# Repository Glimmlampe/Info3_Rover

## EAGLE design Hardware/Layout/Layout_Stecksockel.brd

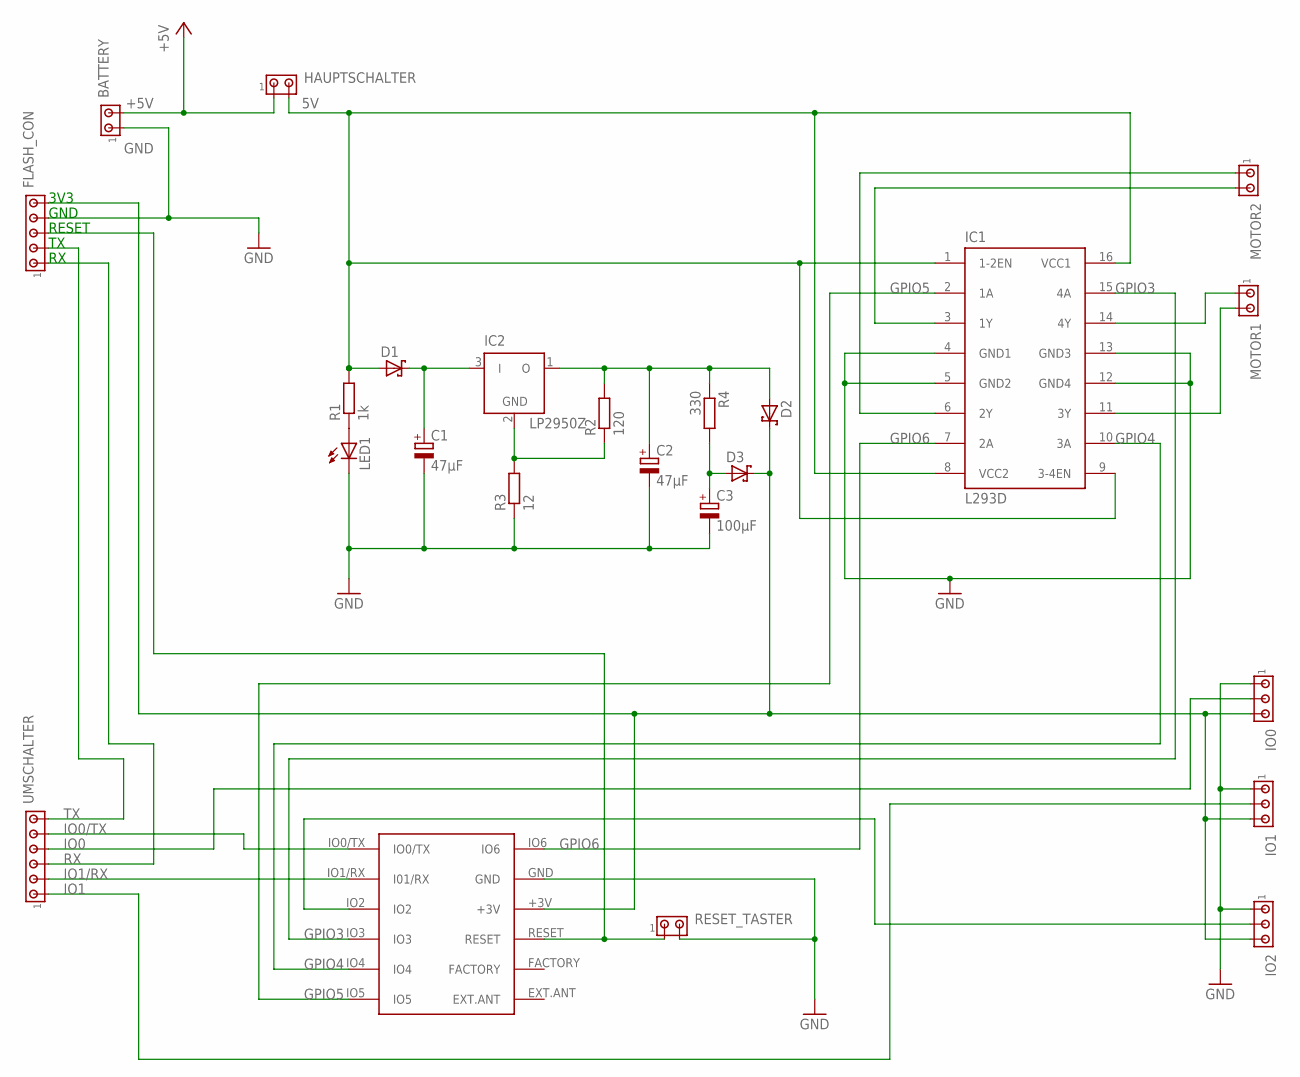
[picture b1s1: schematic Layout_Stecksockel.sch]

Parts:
BATTERY: MTA02-100; 10X02MTA
C1, C2: 47µF; E2,5-6E
C3: 100µF; E2,5-6E
D1, D2, D3: SCHOTTKY-DIODEDO35-7; DO35-7
FLASH_CON: MTA05-100; 10X05MTA
HAUPTSCHALTER: MTA02-100; 10X02MTA
IC1: L293D; DIL16
IC2: LP2950Z; TO92
IO0, IO1, IO2: MTA03-100; 10X03MTA
LED1: LED_ELD260; LED_LD260
MOTOR1, MOTOR2: MTA02-100; 10X02MTA
R1: 1k; 0207/10
R2: 120; 0207/10
R3: 12; 0207/10
R4: 330; 0207/10
RESET_TASTER: MTA02-100; 10X02MTA
U$1: RFDUINO
UMSCHALTER: MTA06-100; 10X06MTA

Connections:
5V: D1.A, HAUPTSCHALTER.2, IC1.1 (1-2EN), IC1.8 (VCC2), IC1.9 (3-4EN), IC1.16 (VCC1), R1.2
+3V: D2.C, D3.C, FLASH_CON.5, IO0.3, IO1.3, IO2.3, U$1.+3V
+5V: BATTERY.2, HAUPTSCHALTER.1
GND: BATTERY.1, C1.-, C2.-, C3.-, FLASH_CON.4, IC1.4 (GND1), IC1.5 (GND2), IC1.12 (GND4), IC1.13 (GND3), IO0.1, IO1.1, IO2.1, LED1.K (C), R3.1, RESET_TASTER.2, U$1.GND
GPIO3: IC1.15 (4A), U$1.IO3
GPIO4: IC1.10 (3A), U$1.IO4
GPIO5: IC1.2 (1A), U$1.IO5
GPIO6: IC1.7 (2A), U$1.IO6
IO0: IO0.2, UMSCHALTER.4
IO0/TX: U$1.IO0/TX, UMSCHALTER.5
IO1: IO1.2, UMSCHALTER.1
IO1/RX: U$1.IO1/RX (I01/RX), UMSCHALTER.2
unnamed: C1.+, D1.C, IC2.3 (I)
unnamed: C3.+, D3.A, R4.2
unnamed: LED1.A, R1.1
unnamed: IC1.6 (2Y), MOTOR2.1
unnamed: IC1.3 (1Y), MOTOR2.2
unnamed: IC2.2 (GND), R2.1, R3.2
unnamed: IC1.11 (3Y), MOTOR1.2
unnamed: IC1.14 (4Y), MOTOR1.1
unnamed: FLASH_CON.3, RESET_TASTER.1, U$1.RESET
unnamed: C2.+, D2.A, IC2.1 (O), R2.2, R4.1
unnamed: IO2.2, U$1.IO2
RX: FLASH_CON.1, UMSCHALTER.3
TX: FLASH_CON.2, UMSCHALTER.6

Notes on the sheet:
RESET
3V3
GND

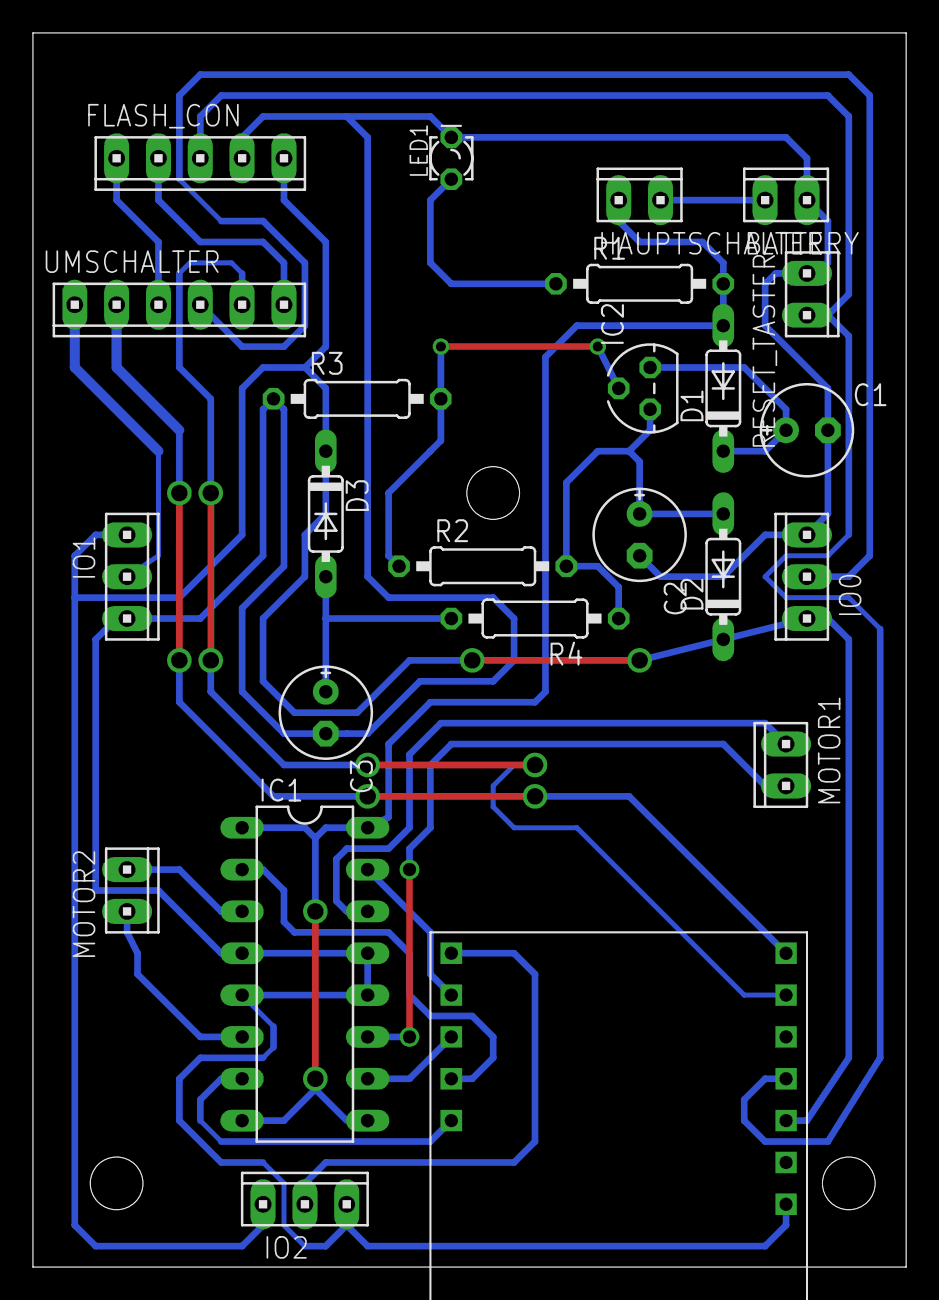
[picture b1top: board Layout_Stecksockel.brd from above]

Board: 2 copper layers, 53.0 x 74.9 mm, 24 parts (0 on the bottom side), 25 nets.

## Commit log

2015-11-03 Added RFduino Projects
    added the RFduino files to the repo
    * Device -> Dongle
    * Host -> Vehicle
2015-11-03 added Control+GUI
    added the Java project for the control programm and the GUI
2017-01-26 rewritten dongle and rover control
2017-01-27 removed all unnecessary stuff
2017-02-10 Added a documentation folder and hardware layouts, board and CAD
